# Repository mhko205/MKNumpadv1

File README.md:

# MKNumpadv1
RP2040 based numpad + variation with RP2040 - Zero

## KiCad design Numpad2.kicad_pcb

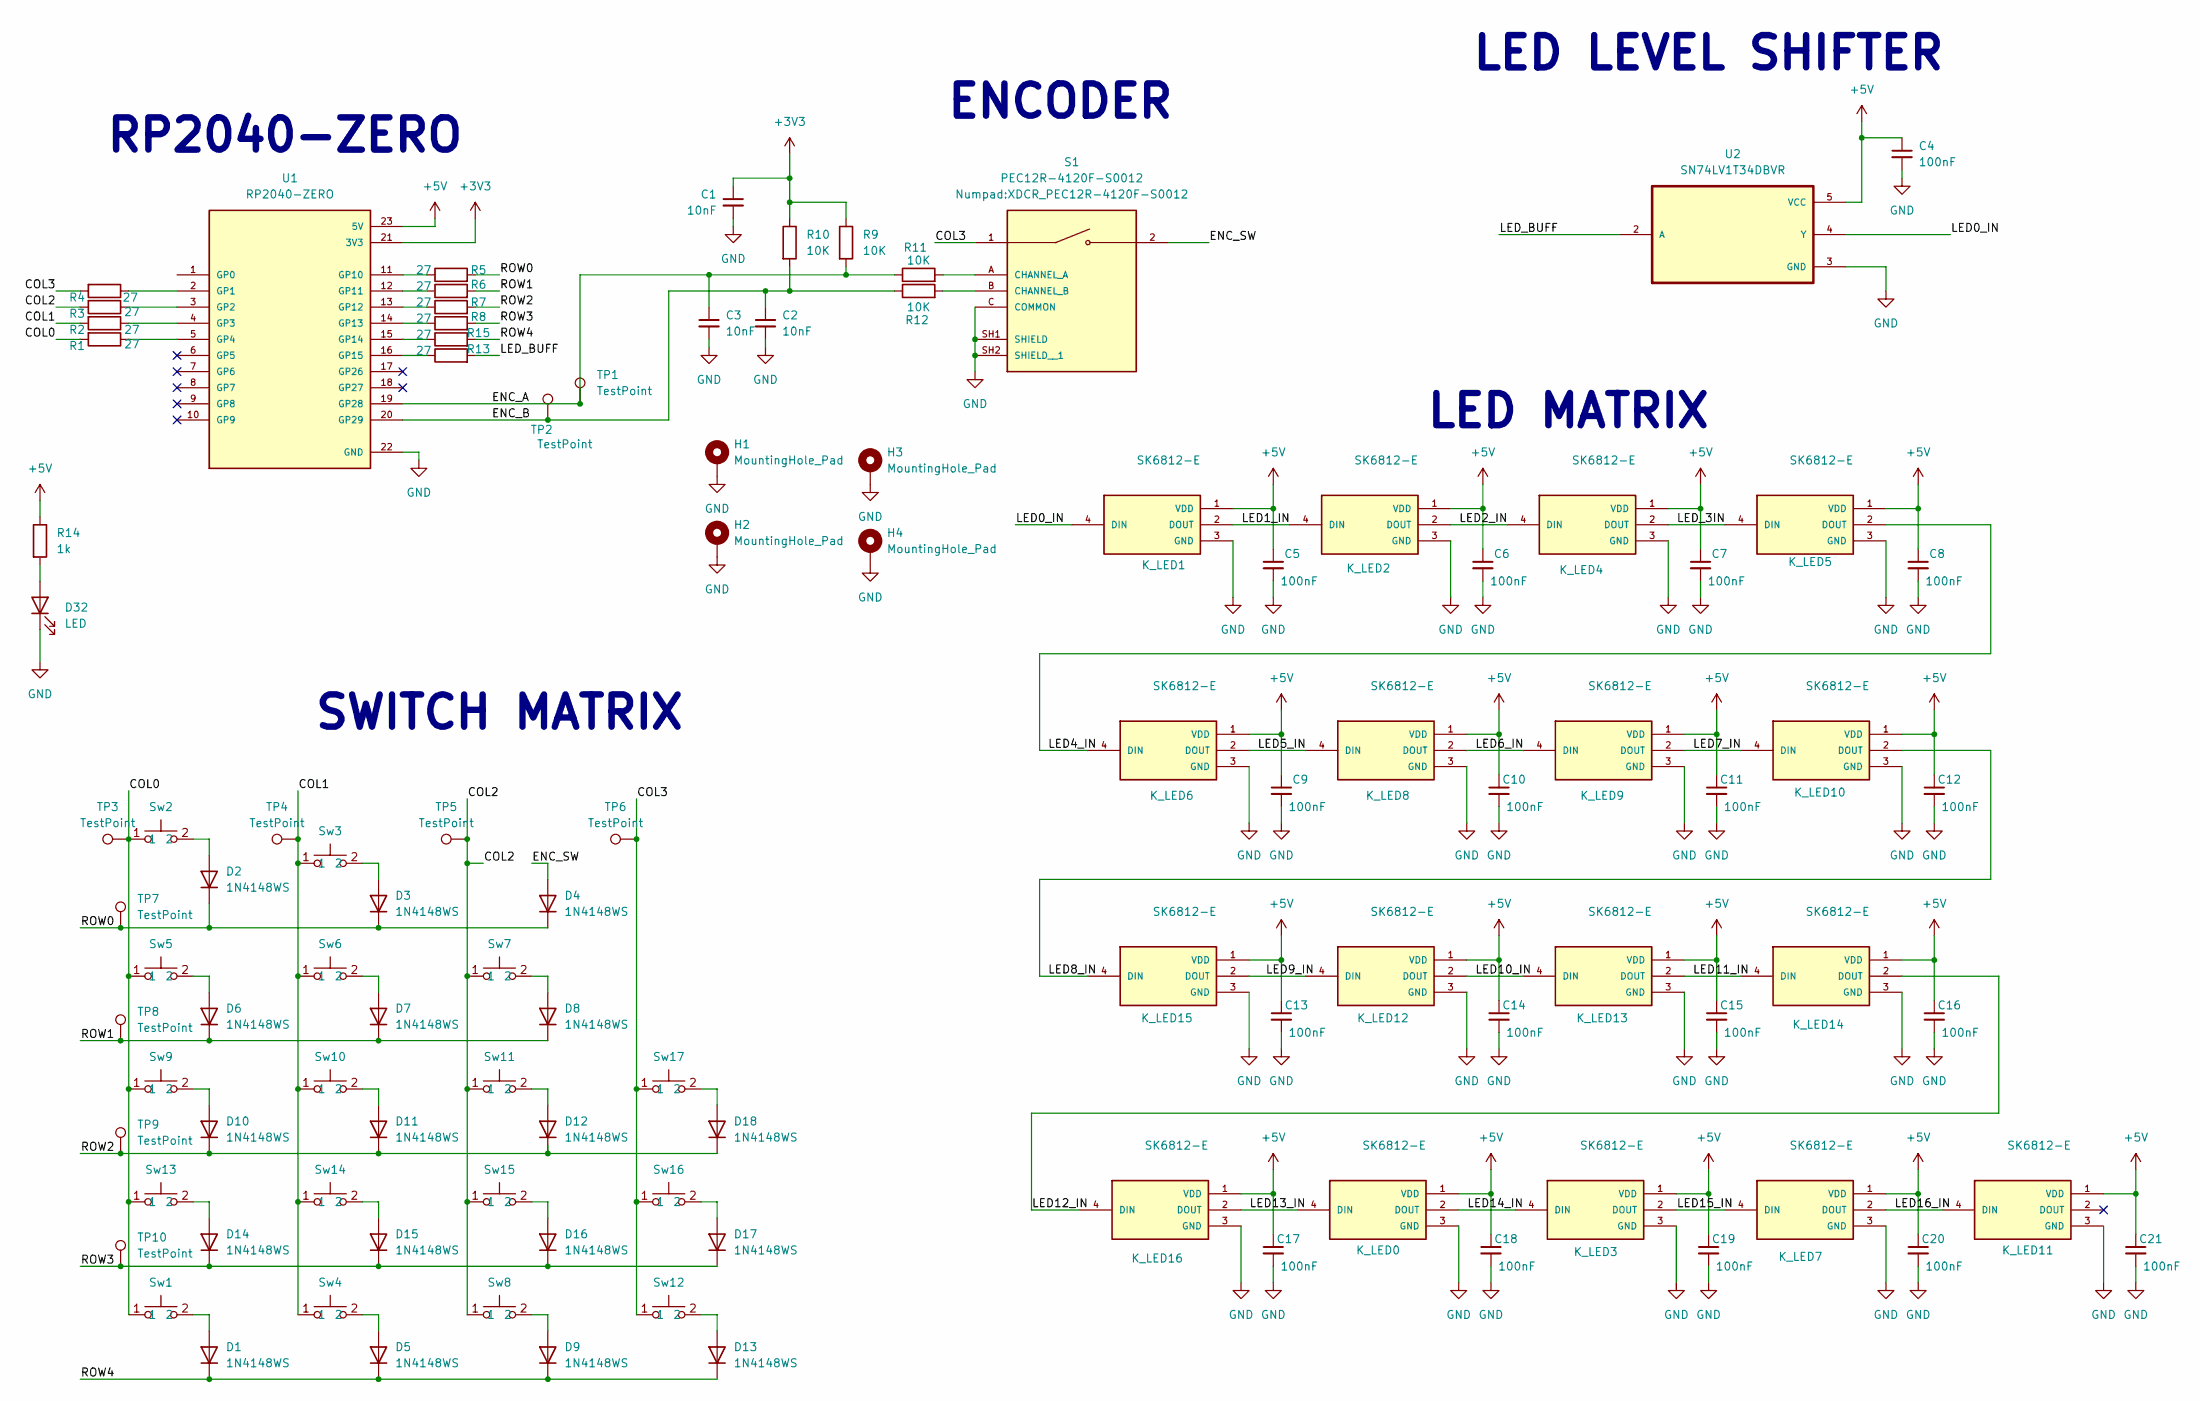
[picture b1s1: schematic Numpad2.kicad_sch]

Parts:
C1, C2, C3: 10nF; C_0402_1005Metric_Pad0.74x0.62mm_HandSolder
C4, C5, C6, C7, C8, C9, C10, C11, C12, C13, C14, C15, C16, C17, C18, C19, C20, C21: 100nF; C_0402_1005Metric_Pad0.74x0.62mm_HandSolder
D1, D2, D3, D4, D5, D6, D7, D8, D9, D10, D11, D12, D13, D14, D15, D16, D17, D18: 1N4148WS; D_SOD-323
D32: LED; LED_0805_2012Metric_Pad1.15x1.40mm_HandSolder
H1, H2, H3, H4: MountingHole_Pad; MountingHole_2.2mm_M2_Pad
K_LED0, K_LED1, K_LED2, K_LED3, K_LED4, K_LED5, K_LED6, K_LED7, K_LED8, K_LED9, K_LED10, K_LED11, K_LED12, K_LED13, K_LED14, K_LED15, K_LED16: SK6812-E; LED_SK6812-E; PARTREV 2
R1, R2, R3, R4, R5, R6, R7, R8, R13, R15: 27; R_0402_1005Metric_Pad0.72x0.64mm_HandSolder
R9, R10, R11, R12: 10K; R_0402_1005Metric_Pad0.72x0.64mm_HandSolder
R14: 1k; R_0402_1005Metric_Pad0.72x0.64mm_HandSolder
S1: PEC12R-4120F-S0012; XDCR_PEC12R-4120F-S0012; PARTREV 07/21
Sw1, Sw2, Sw3, Sw4, Sw5, Sw6, Sw7, Sw8, Sw9, Sw10, Sw11, Sw12, Sw13, Sw14, Sw15, Sw16, Sw17: SW_Hotswap_Kailh_MX
TP1, TP2, TP3, TP4, TP5, TP6, TP7, TP8, TP9, TP10: TestPoint; TestPoint_Pad_1.0x1.0mm
U1: RP2040-ZERO; MODULE_RP2040-ZERO; PARTREV NA
U2: SN74LV1T34DBVR; SOT95P280X145-5N

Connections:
+3V3: C1.1, R9.1, R10.1, U1.21 (3V3)
+5V: C4.1, C5.1, C6.1, C7.1, C8.1, C9.1, C10.1, C11.1, C12.1, C13.1, C14.1, C15.1, C16.1, C17.1, C18.1, C19.1, C20.1, C21.1, K_LED0.1 (VDD), K_LED1.1 (VDD), K_LED2.1 (VDD), K_LED3.1 (VDD), K_LED4.1 (VDD), K_LED5.1 (VDD), K_LED6.1 (VDD), K_LED7.1 (VDD), K_LED8.1 (VDD), K_LED9.1 (VDD), K_LED10.1 (VDD), K_LED11.1 (VDD), K_LED12.1 (VDD), K_LED13.1 (VDD), K_LED14.1 (VDD), K_LED15.1 (VDD), K_LED16.1 (VDD), R14.1, U1.23 (5V), U2.5 (VCC)
/COL0: R1.2, Sw1.1, Sw2.1, Sw5.1, Sw9.1, Sw13.1, TP3.1
/COL1: R2.2, Sw3.1, Sw4.1, Sw6.1, Sw10.1, Sw14.1, TP4.1
/COL2: R3.2, Sw7.1, Sw8.1, Sw11.1, Sw15.1, TP5.1
/COL3: R4.2, S1.1, Sw12.1, Sw16.1, Sw17.1, TP6.1
/ENC_A: C3.1, R9.2, R11.1, TP1.1, U1.19 (GP28)
/ENC_B: C2.1, R10.2, R12.1, TP2.1, U1.20 (GP29)
/ENC_SW: D4.2 (A), S1.2
/LED0_IN: K_LED1.4 (DIN), U2.4 (Y)
/LED1_IN: K_LED1.2 (DOUT), K_LED2.4 (DIN)
/LED2_IN: K_LED2.2 (DOUT), K_LED4.4 (DIN)
/LED4_IN: K_LED5.2 (DOUT), K_LED6.4 (DIN)
/LED5_IN: K_LED6.2 (DOUT), K_LED8.4 (DIN)
/LED6_IN: K_LED8.2 (DOUT), K_LED9.4 (DIN)
/LED7_IN: K_LED9.2 (DOUT), K_LED10.4 (DIN)
/LED8_IN: K_LED10.2 (DOUT), K_LED15.4 (DIN)
/LED9_IN: K_LED12.4 (DIN), K_LED15.2 (DOUT)
/LED10_IN: K_LED12.2 (DOUT), K_LED13.4 (DIN)
/LED11_IN: K_LED13.2 (DOUT), K_LED14.4 (DIN)
/LED12_IN: K_LED14.2 (DOUT), K_LED16.4 (DIN)
/LED13_IN: K_LED0.4 (DIN), K_LED16.2 (DOUT)
/LED14_IN: K_LED0.2 (DOUT), K_LED3.4 (DIN)
/LED15_IN: K_LED3.2 (DOUT), K_LED7.4 (DIN)
/LED16_IN: K_LED7.2 (DOUT), K_LED11.4 (DIN)
/LED_3IN: K_LED4.2 (DOUT), K_LED5.4 (DIN)
/LED_BUFF: R13.2, U2.2 (A)
/ROW0: D2.1 (K), D3.1 (K), D4.1 (K), R5.2, TP7.1
/ROW1: D6.1 (K), D7.1 (K), D8.1 (K), R6.2, TP8.1
/ROW2: D10.1 (K), D11.1 (K), D12.1 (K), D18.1 (K), R7.2, TP9.1
/ROW3: D14.1 (K), D15.1 (K), D16.1 (K), D17.1 (K), R8.2, TP10.1
/ROW4: D1.1 (K), D5.1 (K), D9.1 (K), D13.1 (K), R15.2
GND: C1.2, C2.2, C3.2, C4.2, C5.2, C6.2, C7.2, C8.2, C9.2, C10.2, C11.2, C12.2, C13.2, C14.2, C15.2, C16.2, C17.2, C18.2, C19.2, C20.2, C21.2, D32.1 (K), H1.1, H2.1, H3.1, H4.1, K_LED0.3 (GND), K_LED1.3 (GND), K_LED2.3 (GND), K_LED3.3 (GND), K_LED4.3 (GND), K_LED5.3 (GND), K_LED6.3 (GND), K_LED7.3 (GND), K_LED8.3 (GND), K_LED9.3 (GND), K_LED10.3 (GND), K_LED11.3 (GND), K_LED12.3 (GND), K_LED13.3 (GND), K_LED14.3 (GND), K_LED15.3 (GND), K_LED16.3 (GND), S1.C (COMMON), S1.SH1 (SHIELD), S1.SH2 (SHIELD__1), U1.22 (GND), U2.3 (GND)
unnamed: D1.2 (A), Sw1.2
unnamed: D2.2 (A), Sw2.2
unnamed: D3.2 (A), Sw3.2
unnamed: D5.2 (A), Sw4.2
unnamed: D6.2 (A), Sw5.2
unnamed: D7.2 (A), Sw6.2
unnamed: D8.2 (A), Sw7.2
unnamed: D9.2 (A), Sw8.2
unnamed: D10.2 (A), Sw9.2
unnamed: D11.2 (A), Sw10.2
unnamed: D12.2 (A), Sw11.2
unnamed: D13.2 (A), Sw12.2
unnamed: D14.2 (A), Sw13.2
unnamed: D15.2 (A), Sw14.2
unnamed: D16.2 (A), Sw15.2
unnamed: D17.2 (A), Sw16.2
unnamed: D18.2 (A), Sw17.2
unnamed: D32.2 (A), R14.2
unnamed: R11.2, S1.A (CHANNEL_A)
unnamed: R12.2, S1.B (CHANNEL_B)
unnamed: R4.1, U1.2 (GP1)
unnamed: R3.1, U1.3 (GP2)
unnamed: R2.1, U1.4 (GP3)
unnamed: R1.1, U1.5 (GP4)
unnamed: R5.1, U1.11 (GP10)
unnamed: R6.1, U1.12 (GP11)
unnamed: R7.1, U1.13 (GP12)
unnamed: R8.1, U1.14 (GP13)
unnamed: R15.1, U1.15 (GP14)
unnamed: R13.1, U1.16 (GP15)

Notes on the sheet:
LED MATRIX
ENCODER
SWITCH MATRIX
LED LEVEL SHIFTER
RP2040-ZERO

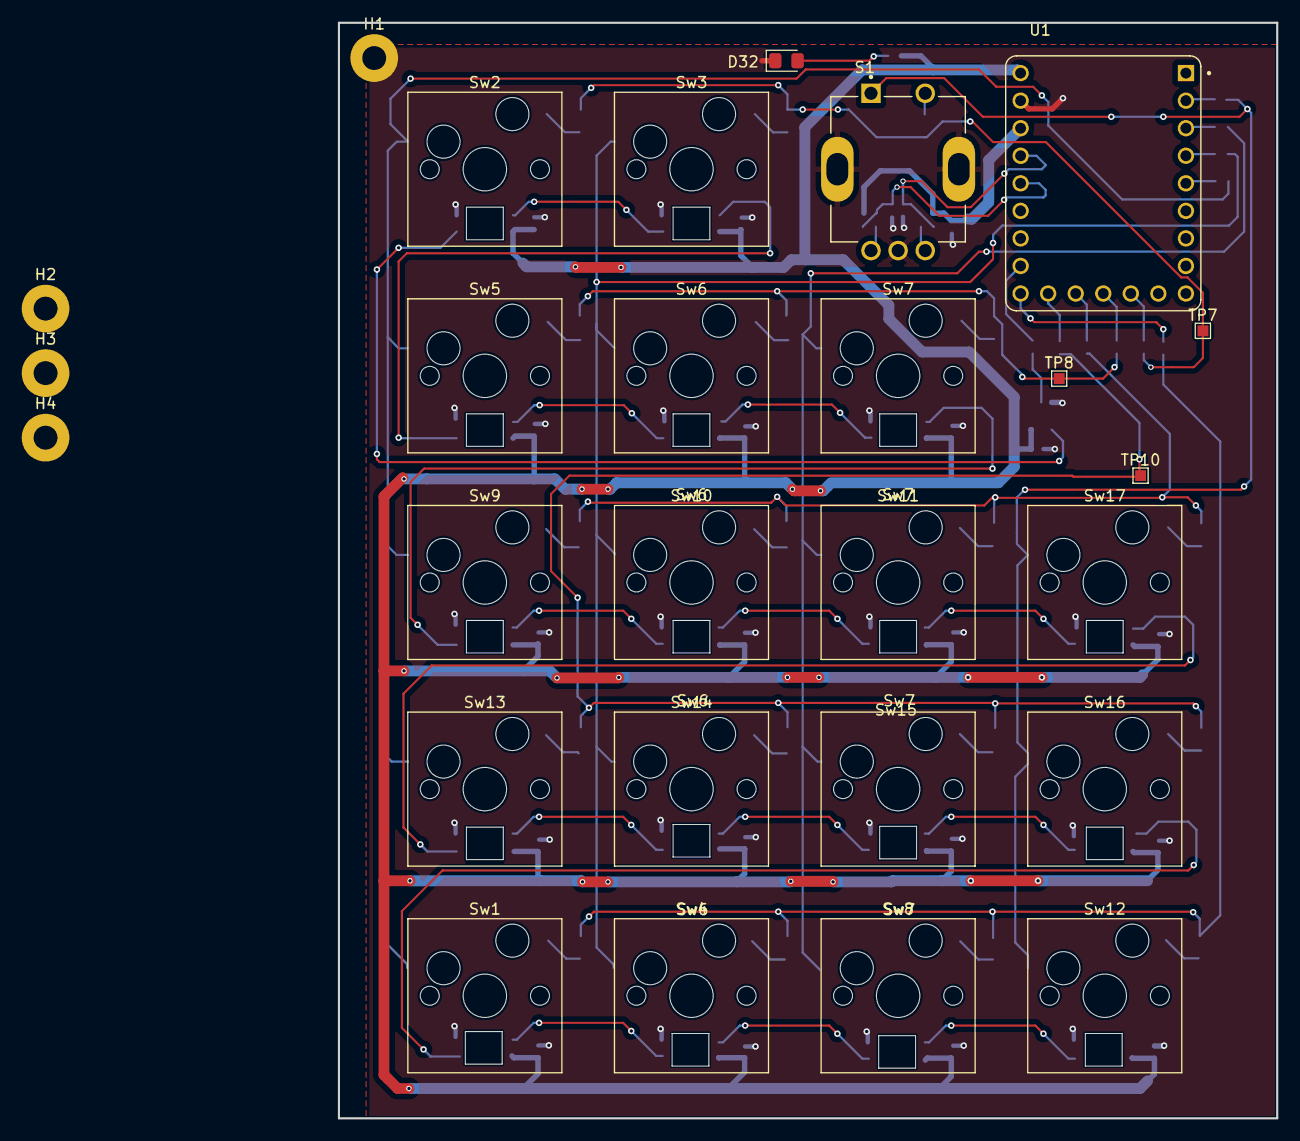
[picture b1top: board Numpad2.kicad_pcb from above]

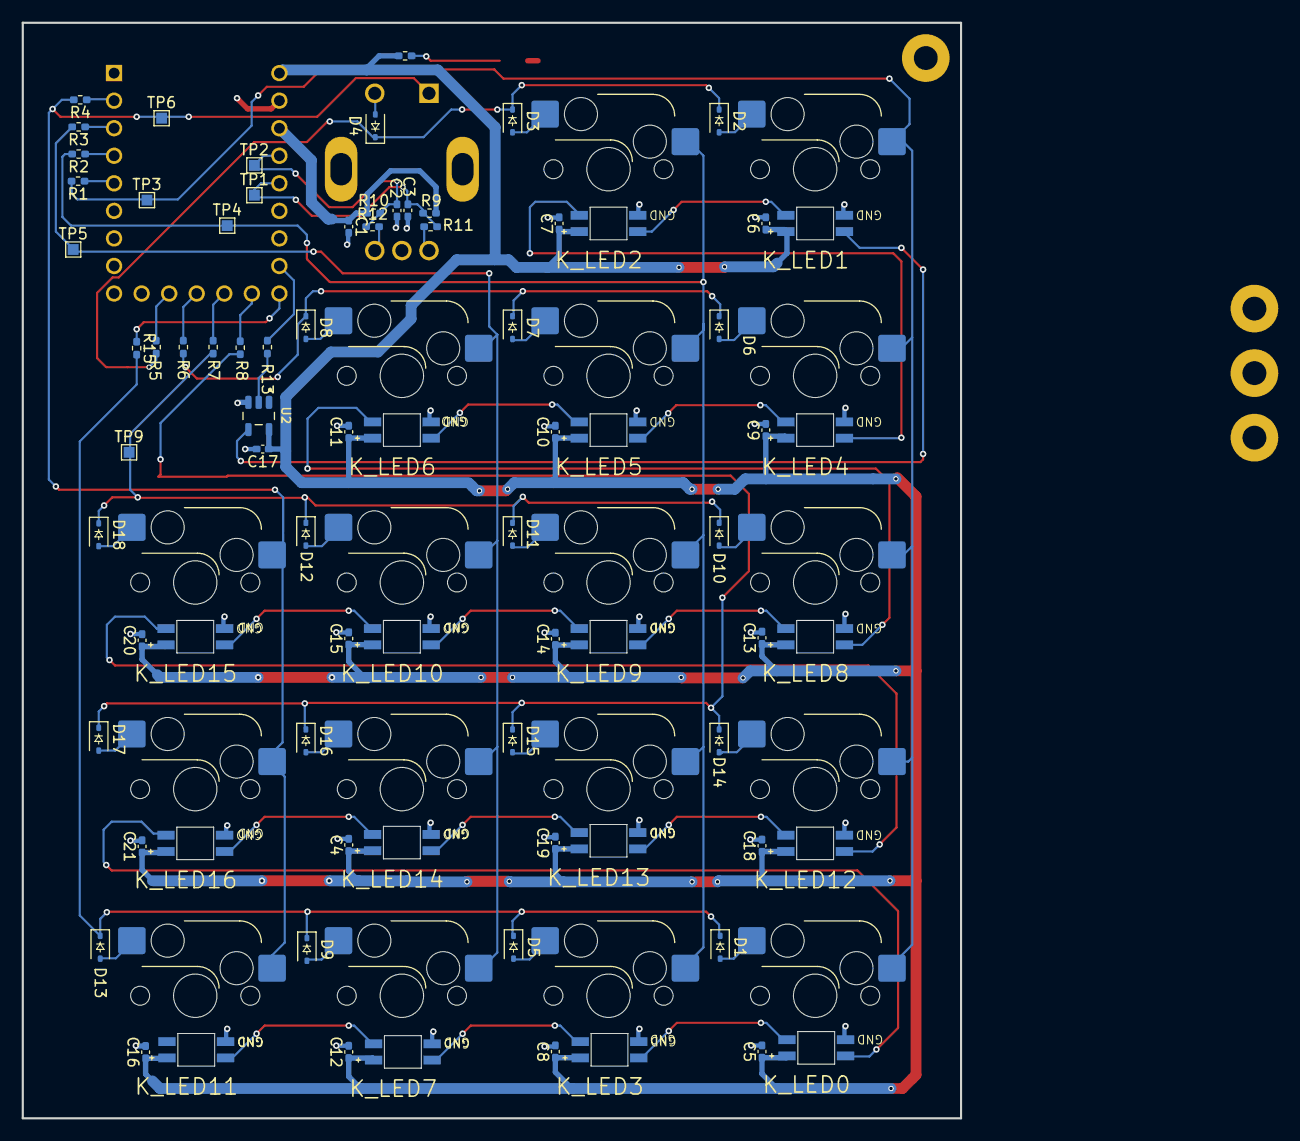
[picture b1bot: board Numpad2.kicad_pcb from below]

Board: 2 copper layers, 86.5 x 101.0 mm, 106 parts (79 on the bottom side), 63 nets.
